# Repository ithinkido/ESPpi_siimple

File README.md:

# ESP_Pi_siimple
 A basic DIY ESP32 to PiPlot adapter board  

To flash firmware - head over to https://ithinkido.github.io/ESPpi_siimple/

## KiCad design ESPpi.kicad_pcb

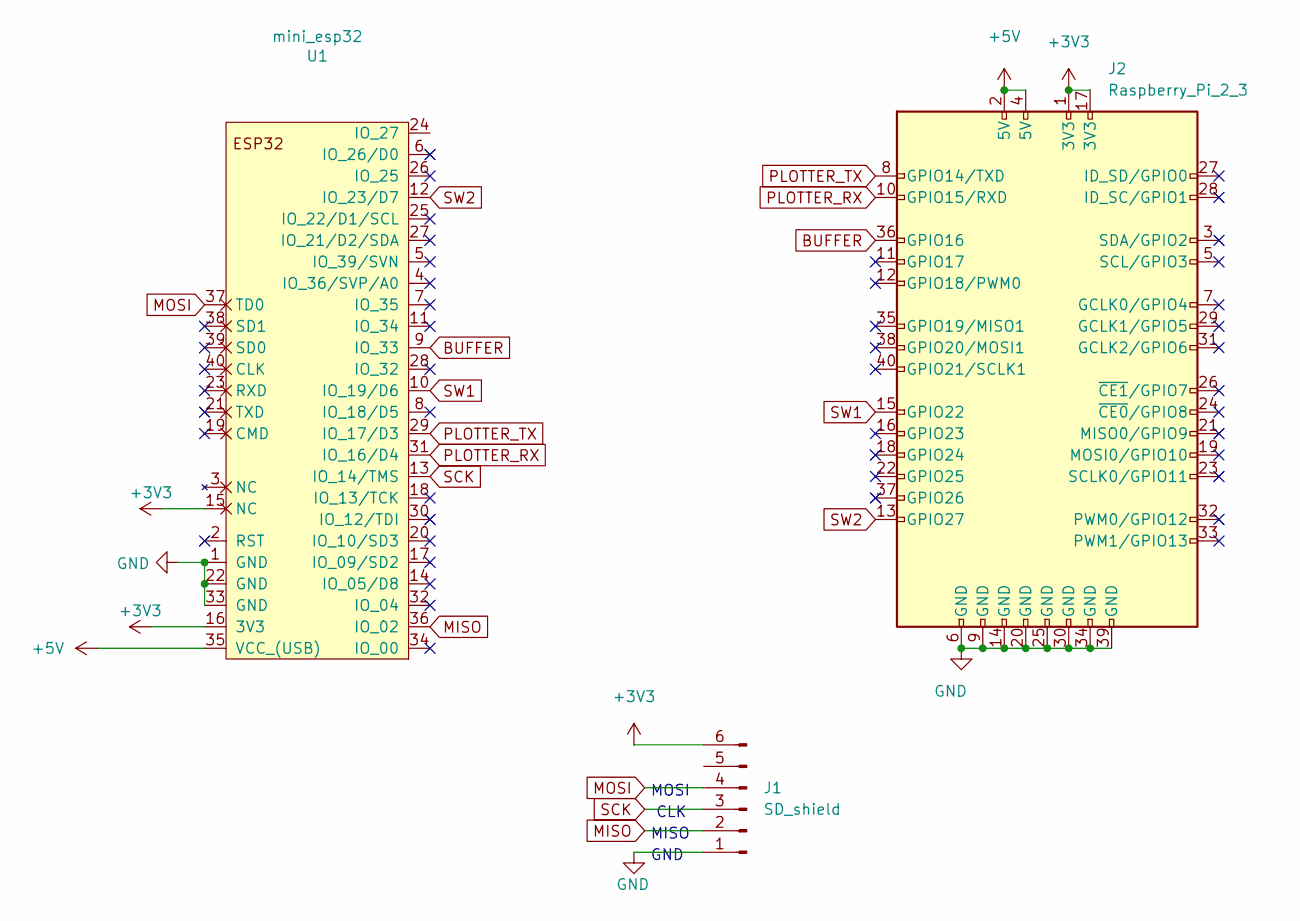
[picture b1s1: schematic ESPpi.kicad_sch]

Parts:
J1: SD_shield; PinHeader_1x06_P2.54mm_Vertical
J2: Raspberry_Pi_2_3; ESP_TO_PI_PLOT
U1: mini_esp32; ESP32_mini

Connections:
+3V3: J1.6, J2.1 (3V3), J2.17 (3V3), U1.15 (NC), U1.16 (3V3)
+5V: J2.2 (5V), J2.4 (5V), U1.35 (VCC_(USB))
BUFFER: J2.36 (GPIO16), U1.9 (IO_33)
GND: J1.1, J2.6 (GND), J2.9 (GND), J2.14 (GND), J2.20 (GND), J2.25 (GND), J2.30 (GND), J2.34 (GND), J2.39 (GND), U1.1 (GND), U1.22 (GND), U1.33 (GND)
MISO: J1.2, U1.36 (IO_02)
MOSI: J1.4, U1.37 (TD0)
PLOTTER_RX: J2.10 (GPIO15/RXD), U1.31 (IO_16/D4)
PLOTTER_TX: J2.8 (GPIO14/TXD), U1.29 (IO_17/D3)
SCK: J1.3, U1.13 (IO_14/TMS)
SW1: J2.15 (GPIO22), U1.10 (IO_19/D6)
SW2: J2.13 (GPIO27), U1.12 (IO_23/D7)

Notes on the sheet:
CLK
GND
MISO
MOSI

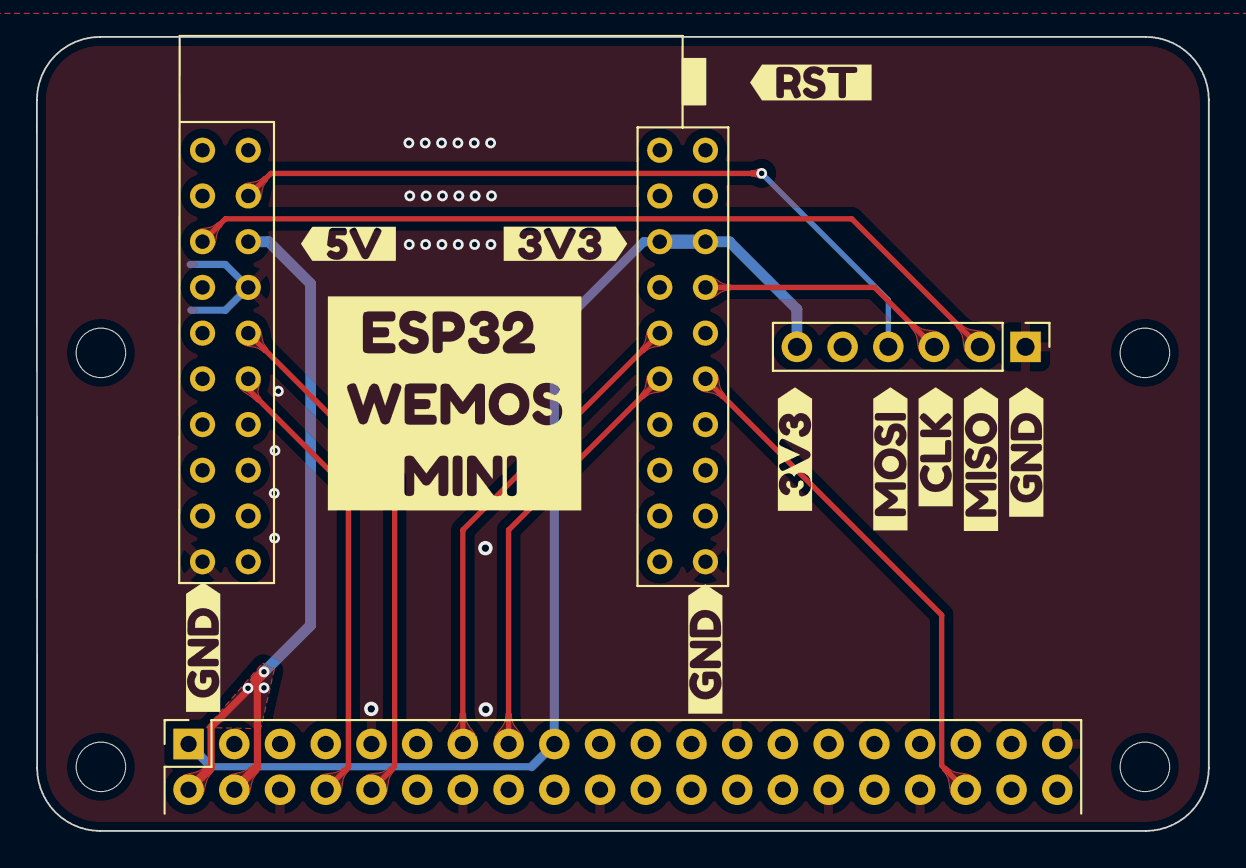
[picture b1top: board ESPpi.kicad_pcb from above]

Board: 2 copper layers, 65.1 x 44.1 mm, 14 parts (0 on the bottom side), 11 nets.

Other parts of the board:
kibuzzard-62B2ECCC: G***; kibuzzard-62B2ECCC
kibuzzard-62B2ECE6, kibuzzard-62B2ECE6#2, kibuzzard-62B2ECE6#3: G***; kibuzzard-62B2ECE6
kibuzzard-62B2ECF6: G***; kibuzzard-62B2ECF6
kibuzzard-62B2ED0A: G***; kibuzzard-62B2ED0A
kibuzzard-62B2ED39: G***; kibuzzard-62B2ED39
kibuzzard-62B2EFA4: G***; kibuzzard-62B2EFA4
kibuzzard-62B2EFEF: G***; kibuzzard-62B2EFEF
kibuzzard-62B2F93B: G***; kibuzzard-62B2F93B
kibuzzard-62B2FA68: G***; kibuzzard-62B2FA68

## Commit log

2022-06-23 Update web tools installer
2022-06-23 Readme
